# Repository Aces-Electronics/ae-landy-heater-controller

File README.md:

<h1 align="center">

  Ace's Electronics Pty Ltd  
  12V heater controller for mirrors and windscreens  
</h1>

# Looking to get up and running?
- [Wiki - Quickstart Guide](../../wiki/Quickstart-Guide)

# Project Goals:
The overall goal of this project is to make a simple, robust and reliable heater controller for vehicles that have heated mirrors and windscreens, like a Land Rover Defender for example. The controller will be solid state and be able to handle up to 30A at 12-14V with a maximum input voltage of 20V.

# Design goals:  
- Smallest form-factor possible while being able to handle 30A without getting too hot
- Simple configuration
- Easy to mount
- Zero maintenance

# JonoTron-3000 v0.3
Version 0.3 was made to address a small issue with the switch pull-up, which was incorrectly tied to 12V instead of 3.3V. The hardware pull-up has been removed completely in ths version as the ESP32 has internal pull-ups that are more than capable.

# JonoTron-3000 v0.2
Version 0.2 was made to addresss a couple of isssues, namely:
- Input and ouputs polarity was swapped, thanks to the xt-60 injection mould anomally that made a - look like a + when I eyeballed it to see which side was negative
- All outputs were tied together and were't individually controllable
- The board couldn't really handle 30A, not safely

Boards are tested and workng well!

v0.2 renders: 

# Where to Buy:
Available to purchase in Australia or New Zealand via <a href="https://d1b959-f7.myshopify.com/">The AE Store</a>

## Support:
Contact me direct via ace<@>aceselectronics.com.au, just make it look like a normal email address. (hiding from the bots ;)

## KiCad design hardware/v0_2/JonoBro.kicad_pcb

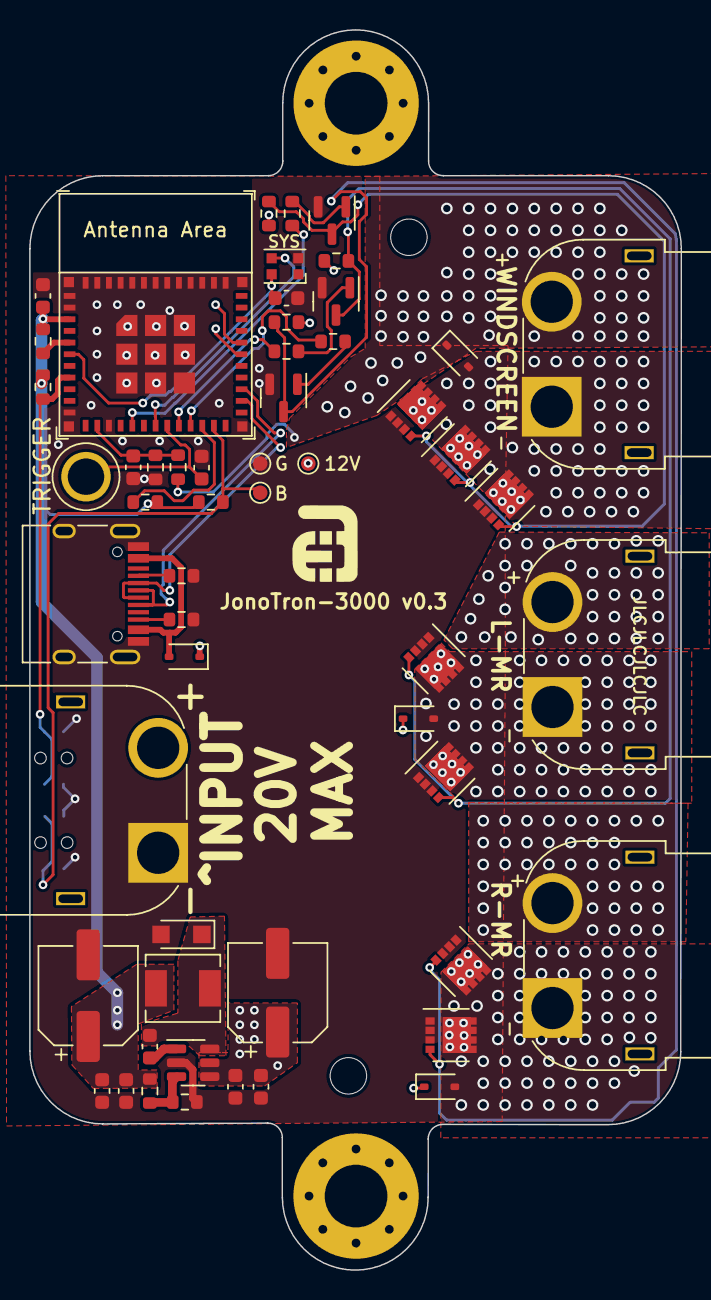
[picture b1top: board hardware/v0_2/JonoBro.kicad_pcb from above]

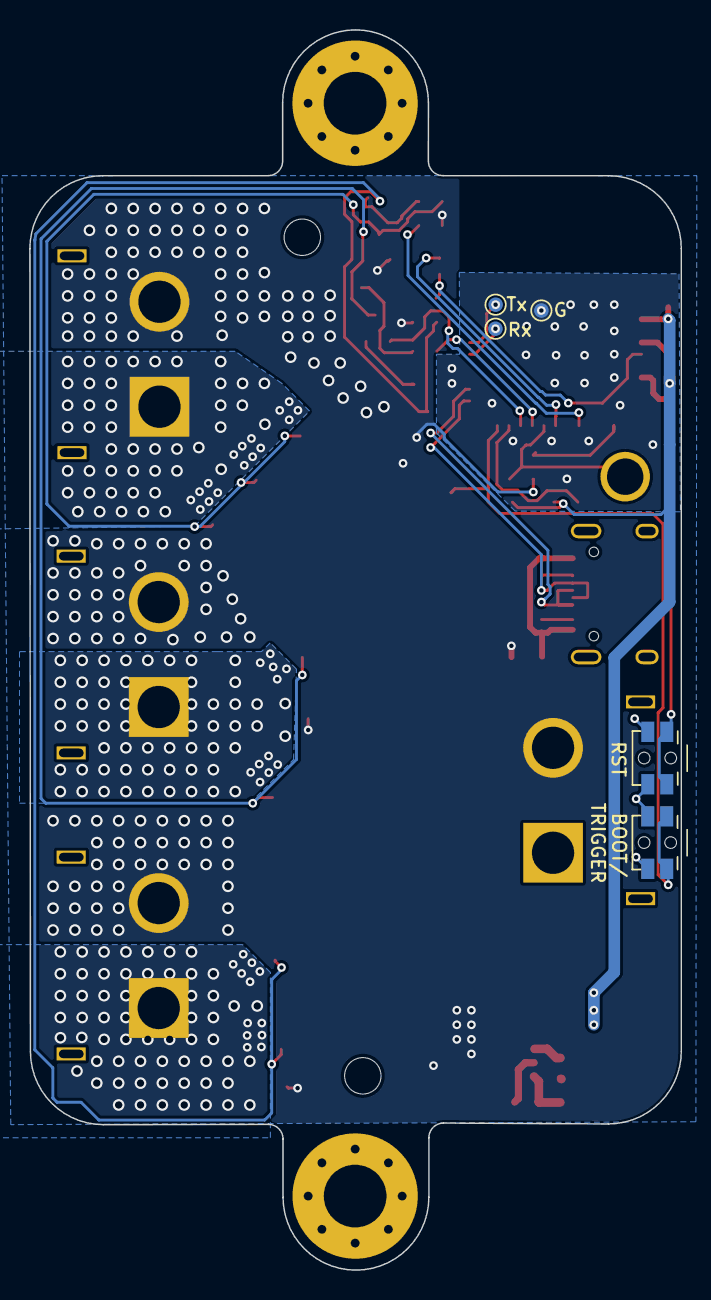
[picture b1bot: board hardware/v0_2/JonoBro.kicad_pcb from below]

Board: 2 copper layers, 44.7 x 85.1 mm, 64 parts (5 on the bottom side), 33 nets.

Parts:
C1: 220uF; CP_Elec_6.3x7.7
C2, C6: 10uF; C_0603_1608Metric
C3, C4, C7, C8, C9, C10, C11: 100nF; C_0603_1608Metric
C5: 22uF; CP_Elec_6.3x5.4
D1: PMEG6020ER; Nexperia_CFP3_SOD-123W
D2: WS2812-2020; LED_WS2812B-2020_PLCC4_2.0x2.0mm
D4, D5, D6, D7: 1N5819WS; D_SOD-323
H1, H2: MountingHole; MountingHole_2.5mm
H3, H4: MountingHole; MountingHole_4.3mm_M4_Pad_Via
J1, J2, J3: Conn_01x02_Pin; AMASS_XT60PW-F_1x02_P7.20mm_Horizontal
J4: Conn_01x02_Pin; AMASS_XT60PW-M_1x02_P7.20mm_Horizontal
J6: USB_C_Receptacle_USB2.0; USB_C_Receptacle_HRO_TYPE-C-31-M-12
L1: 10uH; L_Chilisin_BMRA00040415
Q1, Q3, Q5, Q6, Q8, Q9, Q10: CSD19537Q3; VSON-8_3.3x3.3mm_P0.65mm_NexFET
Q2, Q4, Q7: MMBT3904; SOT-23
R1, R5, R7, R9, R10, R11, R12, R16, R18: 13k; R_0603_1608Metric
R2: 4.3k; R_0603_1608Metric
R4: 2.2k; R_0603_1608Metric
R8, R15, R17: 1k; R_0603_1608Metric
R13, R14: 5.1k; R_0603_1608Metric
SW1, SW2: SW_Push; ALPSALPINE-SKSCLBE010_C115361
TP1, TP2, TP4, TP5, TP6, TP8: TestPoint; TestPoint_Pad_D1.0mm
TP3: TestPoint; TestPoint_Loop_D3.80mm_Drill2.5mm
U1: AOZ1280CI; SOT-23-6
U2: ESP32-C3-MINI-1

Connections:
+3.3V: C5.1, C6.1, C7.1, C8.1, L1.2, R1.1, R5.1, R10.1, R11.1, R12.1, U2.3 (3V3)
+12V: C1.1, C2.1, C3.1, D4.1 (K), D5.1 (K), D6.1 (K), D7.1 (K), J1.2, J2.2, J3.2, J4.2, R7.1, R9.1, R16.1, R18.1, TP8.1, U1.4 (EN), U1.5 (VIN)
GND: C1.2, C2.2, C3.2, C5.2, C6.2, C7.2, C8.2, C9.2, C10.2, C11.2, D1.2 (A), D2.2 (GND), J4.1, J6.A1 (GND), J6.A12 (GND), J6.B1 (GND), J6.B12 (GND), J6.S1 (SHIELD), Q1.1 (S), Q1.2 (S), Q1.3 (S), Q2.2 (E), Q3.1 (S), Q3.2 (S), Q3.3 (S), Q4.2 (E), Q5.1 (S), Q5.2 (S), Q5.3 (S), Q6.1 (S), Q6.2 (S), Q6.3 (S), Q7.2 (E), Q8.1 (S), Q8.2 (S), Q8.3 (S), Q9.1 (S), Q9.2 (S), Q9.3 (S), Q10.1 (S), Q10.2 (S), Q10.3 (S), R2.2, R4.1, R13.1, R14.1, SW1.2, SW2.2, TP2.1, TP6.1, U1.2 (GND), U2.1 (GND), U2.2 (GND), U2.11 (GND), U2.14 (GND), U2.36 (GND), U2.37 (GND), U2.38 (GND), U2.39 (GND), U2.40 (GND), U2.41 (GND), U2.42 (GND), U2.43 (GND), U2.44 (GND), U2.45 (GND), U2.46 (GND), U2.47 (GND), U2.48 (GND), U2.49 (GND), U2.50 (GND), U2.51 (GND), U2.52 (GND), U2.53 (GND)
MOSFET_LMR: R17.1, U2.20 (GPIO6)
MOSFET_RMR: R15.1, U2.21 (GPIO7)
MOSFET_WS: R8.1, U2.16 (GPIO10)
unnamed: C4.2, D1.1 (K), L1.1, U1.6 (LX)
unnamed: D4.2 (A), J3.1, Q1.5 (D), Q3.5 (D), Q10.5 (D)
unnamed: D6.2 (A), J2.1, Q5.5 (D), Q6.5 (D)
unnamed: D7.2 (A), J1.1, Q8.5 (D), Q9.5 (D)
unnamed: J6.A5 (CC1), R13.2
unnamed: J6.B5 (CC2), R14.2
unnamed: Q1.4 (G), Q2.3 (C), Q3.4 (G), Q10.4 (G), R9.2
unnamed: Q2.1 (B), R8.2
unnamed: Q4.1 (B), R15.2
unnamed: Q4.3 (C), Q5.4 (G), Q6.4 (G), R16.2
unnamed: Q7.1 (B), R17.2
unnamed: Q7.3 (C), Q8.4 (G), Q9.4 (G), R18.2
unnamed: C4.1, U1.1 (BST)
unnamed: R1.2, R2.1, U1.3 (FB)
unnamed: R5.2, SW1.1, U2.8 (EN/CHIP_PU)
unnamed: R10.2, U2.5 (GPIO2/ADC1_CH2)
unnamed: R11.2, U2.22 (GPIO8)
unnamed: R12.2, SW2.1, TP1.1, U2.23 (GPIO9)
unnamed: TP5.1, U2.30 (GPIO20/U0RXD)
unnamed: TP4.1, U2.31 (GPIO21/U0TXD)
PXL: D2.3 (DI), U2.18 (GPIO4/ADC1_CH4)
PXL_PWR: C11.1, D2.4 (VDD), U2.6 (GPIO3/ADC1_CH3)
SWITCH: C9.1, TP3.1, U2.19 (GPIO5/ADC2_CH0)
USBD+: J6.A6 (D+), J6.B6 (D+), U2.27 (GPIO19/USB_D+)
USBD-: J6.A7 (D-), J6.B7 (D-), U2.26 (GPIO18/USB_D-)
USB_VBUS: D5.2 (A), J6.A4 (VBUS), J6.A9 (VBUS), J6.B4 (VBUS), J6.B9 (VBUS)
VIn: C10.1, R4.2, R7.2, U2.13 (GPIO1/ADC1_CH1/XTAL_32K_N)

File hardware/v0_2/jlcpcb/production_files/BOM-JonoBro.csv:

Comment,Designator,Footprint,LCSC
SW_Push,"SW1,SW2",ALPSALPINE-SKSCLBE010_C115361,C115361
100nF,C11,C_0603_1608Metric,C1525
USB_C_Receptacle_USB2.0,J6,USB_C_Receptacle_HRO_TYPE-C-31-M-12,C165948
1k,"R15,R17,R8",R_0603_1608Metric,C21190
13k,"R1,R10,R11,R12,R16,R18,R19,R5,R7,R9",R_0603_1608Metric,C22797
4.3k,R2,R_0603_1608Metric,C23159
5.1k,"R13,R14",R_0603_1608Metric,C23186
10uH,L1,L_Chilisin_BMRA00040415,C2847473
1N5819WS,"D4,D5,D6,D7",D_SOD-323,C2927280
100nF,"C10,C2,C3,C4,C6,C7,C8,C9",C_0603_1608Metric,C30926
CSD19537Q3,"Q1,Q10,Q3,Q5,Q6,Q8,Q9",VSON-8_3.3x3.3mm_P0.65mm_NexFET,C315567
220uF,C1,CP_Elec_6.3x7.7,C340768
2.2k,R4,R_0603_1608Metric,C4190
Conn_01x02_Pin,"J1,J2,J3",AMASS_XT60PW-F_1x02_P7.20mm_Horizontal,C428722
AOZ1280CI,U1,SOT-23-6,C5123971
ESP32-C3-MINI-1,U2,ESP32-C3-MINI-1,C5290152
MMBT3904,"Q2,Q4,Q7",SOT-23,C8512
WS2812-2020,D2,LED_WS2812B-2020_PLCC4_2.0x2.0mm,C965555
PMEG6020ER,D1,Nexperia_CFP3_SOD-123W,C98663
Conn_01x02_Pin,J4,AMASS_XT60PW-M_1x02_P7.20mm_Horizontal,C98732
22uF,C5,CP_Elec_6.3x5.4,C98744

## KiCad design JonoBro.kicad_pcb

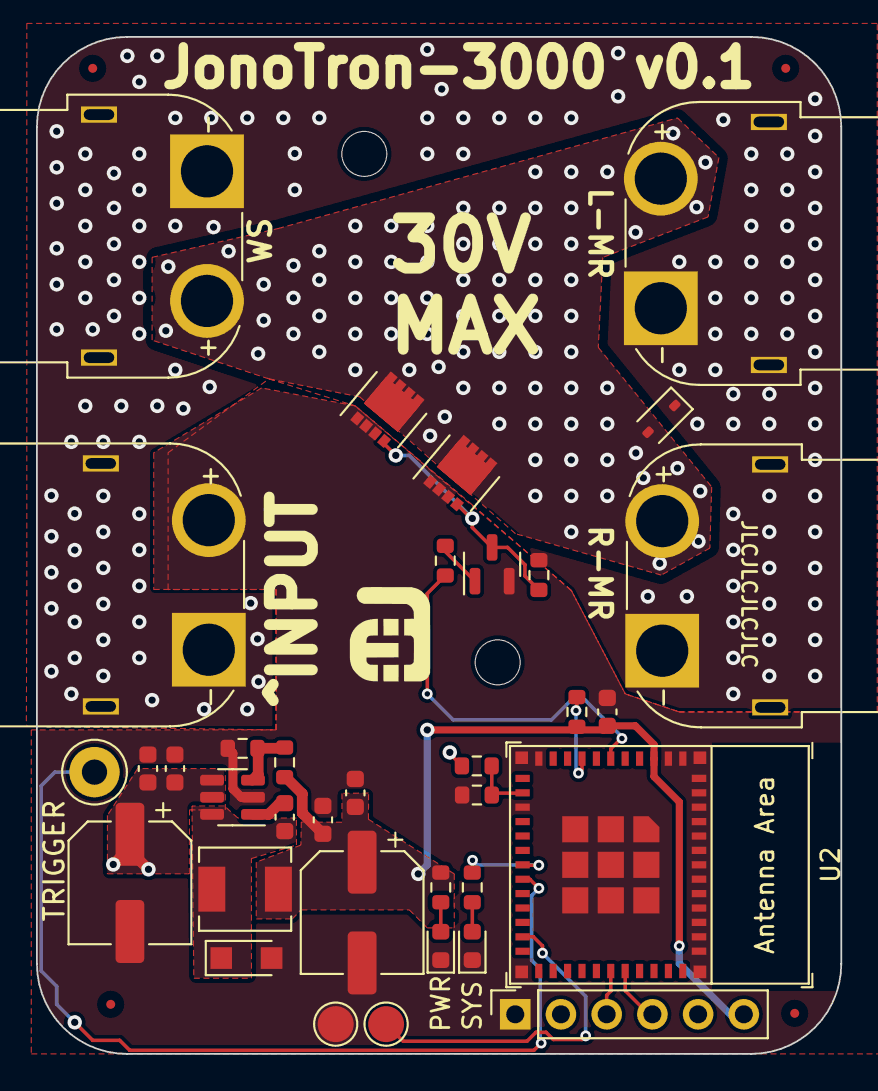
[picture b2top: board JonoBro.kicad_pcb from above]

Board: 2 copper layers, 44.7 x 56.5 mm, 41 parts (0 on the bottom side), 19 nets.

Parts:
C1: 220uF; CP_Elec_6.3x7.7
C2, C6: 10uF; C_0603_1608Metric
C3, C4, C7, C8: 100nF; C_0603_1608Metric
C5: 22uF; CP_Elec_6.3x5.4
D1: PMEG6020ER; Nexperia_CFP3_SOD-123W
D2, D3: LED_Small; LED_0603_1608Metric
D4: 1N5819WS; D_SOD-323
FID1, FID2, FID3, FID4: Fiducial; Fiducial_0.5mm_Mask1.5mm
H1, H2: MountingHole; MountingHole_2.5mm
J1, J2, J3: Conn_01x02_Pin; AMASS_XT60PW-F_1x02_P7.20mm_Horizontal
J4: Conn_01x02_Pin; AMASS_XT60PW-M_1x02_P7.20mm_Horizontal
J5: Conn_01x06_Socket; PinSocket_1x06_P2.54mm_Vertical
L1: 10uH; L_Chilisin_BMRA00040415
Q1, Q3: CSD19537Q3; VSON-8_3.3x3.3mm_P0.65mm_NexFET
Q2: MMBT3904; SOT-23
R1, R5, R7, R9: 13k; R_0603_1608Metric
R2: 4.3k; R_0603_1608Metric
R3, R4, R6: 2.2k; R_0603_1608Metric
R8: 1k; R_0603_1608Metric
TP1, TP2: TestPoint; TestPoint_Pad_D2.0mm
TP3: TestPoint; TestPoint_Loop_D3.50mm_Drill1.4mm_Beaded
U1: AOZ1280CI; SOT-23-6
U2: ESP32-C3-MINI-1

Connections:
+3.3V: C5.1, C6.1, C7.1, C8.1, J5.6, L1.2, R1.1, R3.2, R5.1, U2.3 (3V3)
+12V: C1.1, C2.1, C3.1, D4.1 (K), J1.1, J2.1, J3.1, J4.1, R7.1, R9.1, U1.4 (EN), U1.5 (VIN)
GND: C1.2, C2.2, C3.2, C5.2, C6.2, C7.2, C8.2, D1.2 (A), D2.1 (K), D3.1 (K), J4.2, J5.1, Q1.1 (S), Q1.2 (S), Q1.3 (S), Q2.2 (E), Q3.1 (S), Q3.2 (S), Q3.3 (S), R2.2, R4.1, TP2.1, U1.2 (GND), U2.1 (GND), U2.2 (GND), U2.11 (GND), U2.14 (GND), U2.36 (GND), U2.37 (GND), U2.38 (GND), U2.39 (GND), U2.40 (GND), U2.41 (GND), U2.42 (GND), U2.43 (GND), U2.44 (GND), U2.45 (GND), U2.46 (GND), U2.47 (GND), U2.48 (GND), U2.49 (GND), U2.50 (GND), U2.51 (GND), U2.52 (GND), U2.53 (GND)
MOSFET: R8.1, U2.6 (GPIO3/ADC1_CH3)
unnamed: C4.2, D1.1 (K), L1.1, U1.6 (LX)
unnamed: D2.2 (A), R3.1
unnamed: D3.2 (A), R6.1
unnamed: D4.2 (A), J1.2, J2.2, J3.2, Q1.5 (D), Q3.5 (D)
unnamed: J5.3, U2.30 (GPIO20/U0RXD)
unnamed: J5.4, U2.31 (GPIO21/U0TXD)
unnamed: Q1.4 (G), Q2.3 (C), Q3.4 (G), R9.2
unnamed: Q2.1 (B), R8.2
unnamed: C4.1, U1.1 (BST)
unnamed: R1.2, R2.1, U1.3 (FB)
unnamed: R5.2, U2.8 (EN/CHIP_PU)
unnamed: TP1.1, U2.23 (GPIO9)
SWITCH: TP3.1, U2.19 (GPIO5/ADC2_CH0)
SYS_LED: R6.2, U2.18 (GPIO4/ADC1_CH4)
VIn: R4.2, R7.2, U2.13 (GPIO1/ADC1_CH1/XTAL_32K_N)

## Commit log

2023-09-06 first push
2023-09-07 seems good to me
2023-09-07 added pdf and png
2023-09-07 changed png
2023-09-07 changed pcb
2023-09-08 v0.1 submitted for PCBA
2023-09-08 v0.1 submitted for PCBA take 2
2023-10-03 moved things around
2023-10-05 Working on the code
2023-10-05 updated the image
2023-10-05 pcb updates to 0.2
2023-10-09 WIP, mostly working v0.1
2023-10-11 0.2 wip
2023-10-11 added switch control, preferences, timeout
2023-10-17 bug fixes
2023-10-20 clean and publish
2023-10-20 typos
2023-10-21 moving thisngs around
2023-10-21 moving more stuff around
2023-10-21 added tracbox config for testing
2023-10-22 working with captive portal
2023-10-22 before merge
2023-10-22 updated wiring diagram
2023-10-23 placeholder
2023-10-23 captive portal working
2024-05-13 v0.2 complete JLCPCB
2024-05-27 Starting work on 0.2
2024-05-27 Logging and NeoPixel working
2024-05-27 Fixed logging
2024-05-27 basic functionality working, no switching yet
2024-07-07 WIP, parameters saving
2024-07-07 WIP WiFiManager
2024-07-08 board updates
2024-07-08 portal broken
2024-07-08 removed logging
2024-07-08 back in business
2024-09-01 Finalyy getting the code into shape
2024-09-01 more fixes
2024-09-01 formatting
2024-09-01 small fixes
2024-09-02 moving onto auto updater
2024-09-02 OTA working
2024-09-02 Seems to be working as expected, minus testing
2024-09-03 added WiFi on LED feedback
2024-09-03 Detect voltage source
2024-09-03 lots of small fixes
2024-09-03 small fix
2024-09-03 Check on first connect
2024-09-10 Update README.md
    Added wiki link
2024-09-10 Update README.md
    typo
2024-09-10 Update README.md
    link fixes
2024-09-12 Adding 3D models
2024-09-12 Adding AE Equipped sticker
2024-09-12 Adding JonoTron renders
2024-09-12 v0.3 updates
2024-09-12 readme
2024-09-12 readme update
2024-09-12 readme updates
2024-09-24 Closing in on a real release
2024-09-24 Maybe CI?
2024-09-24 Fixing paths
2024-09-24 fixing CI?
2024-09-24 testing
2024-09-24 first production release!
2025-07-11 Updates for OTA library
2025-07-11 testing the timer
2025-07-11 Fixing CI
